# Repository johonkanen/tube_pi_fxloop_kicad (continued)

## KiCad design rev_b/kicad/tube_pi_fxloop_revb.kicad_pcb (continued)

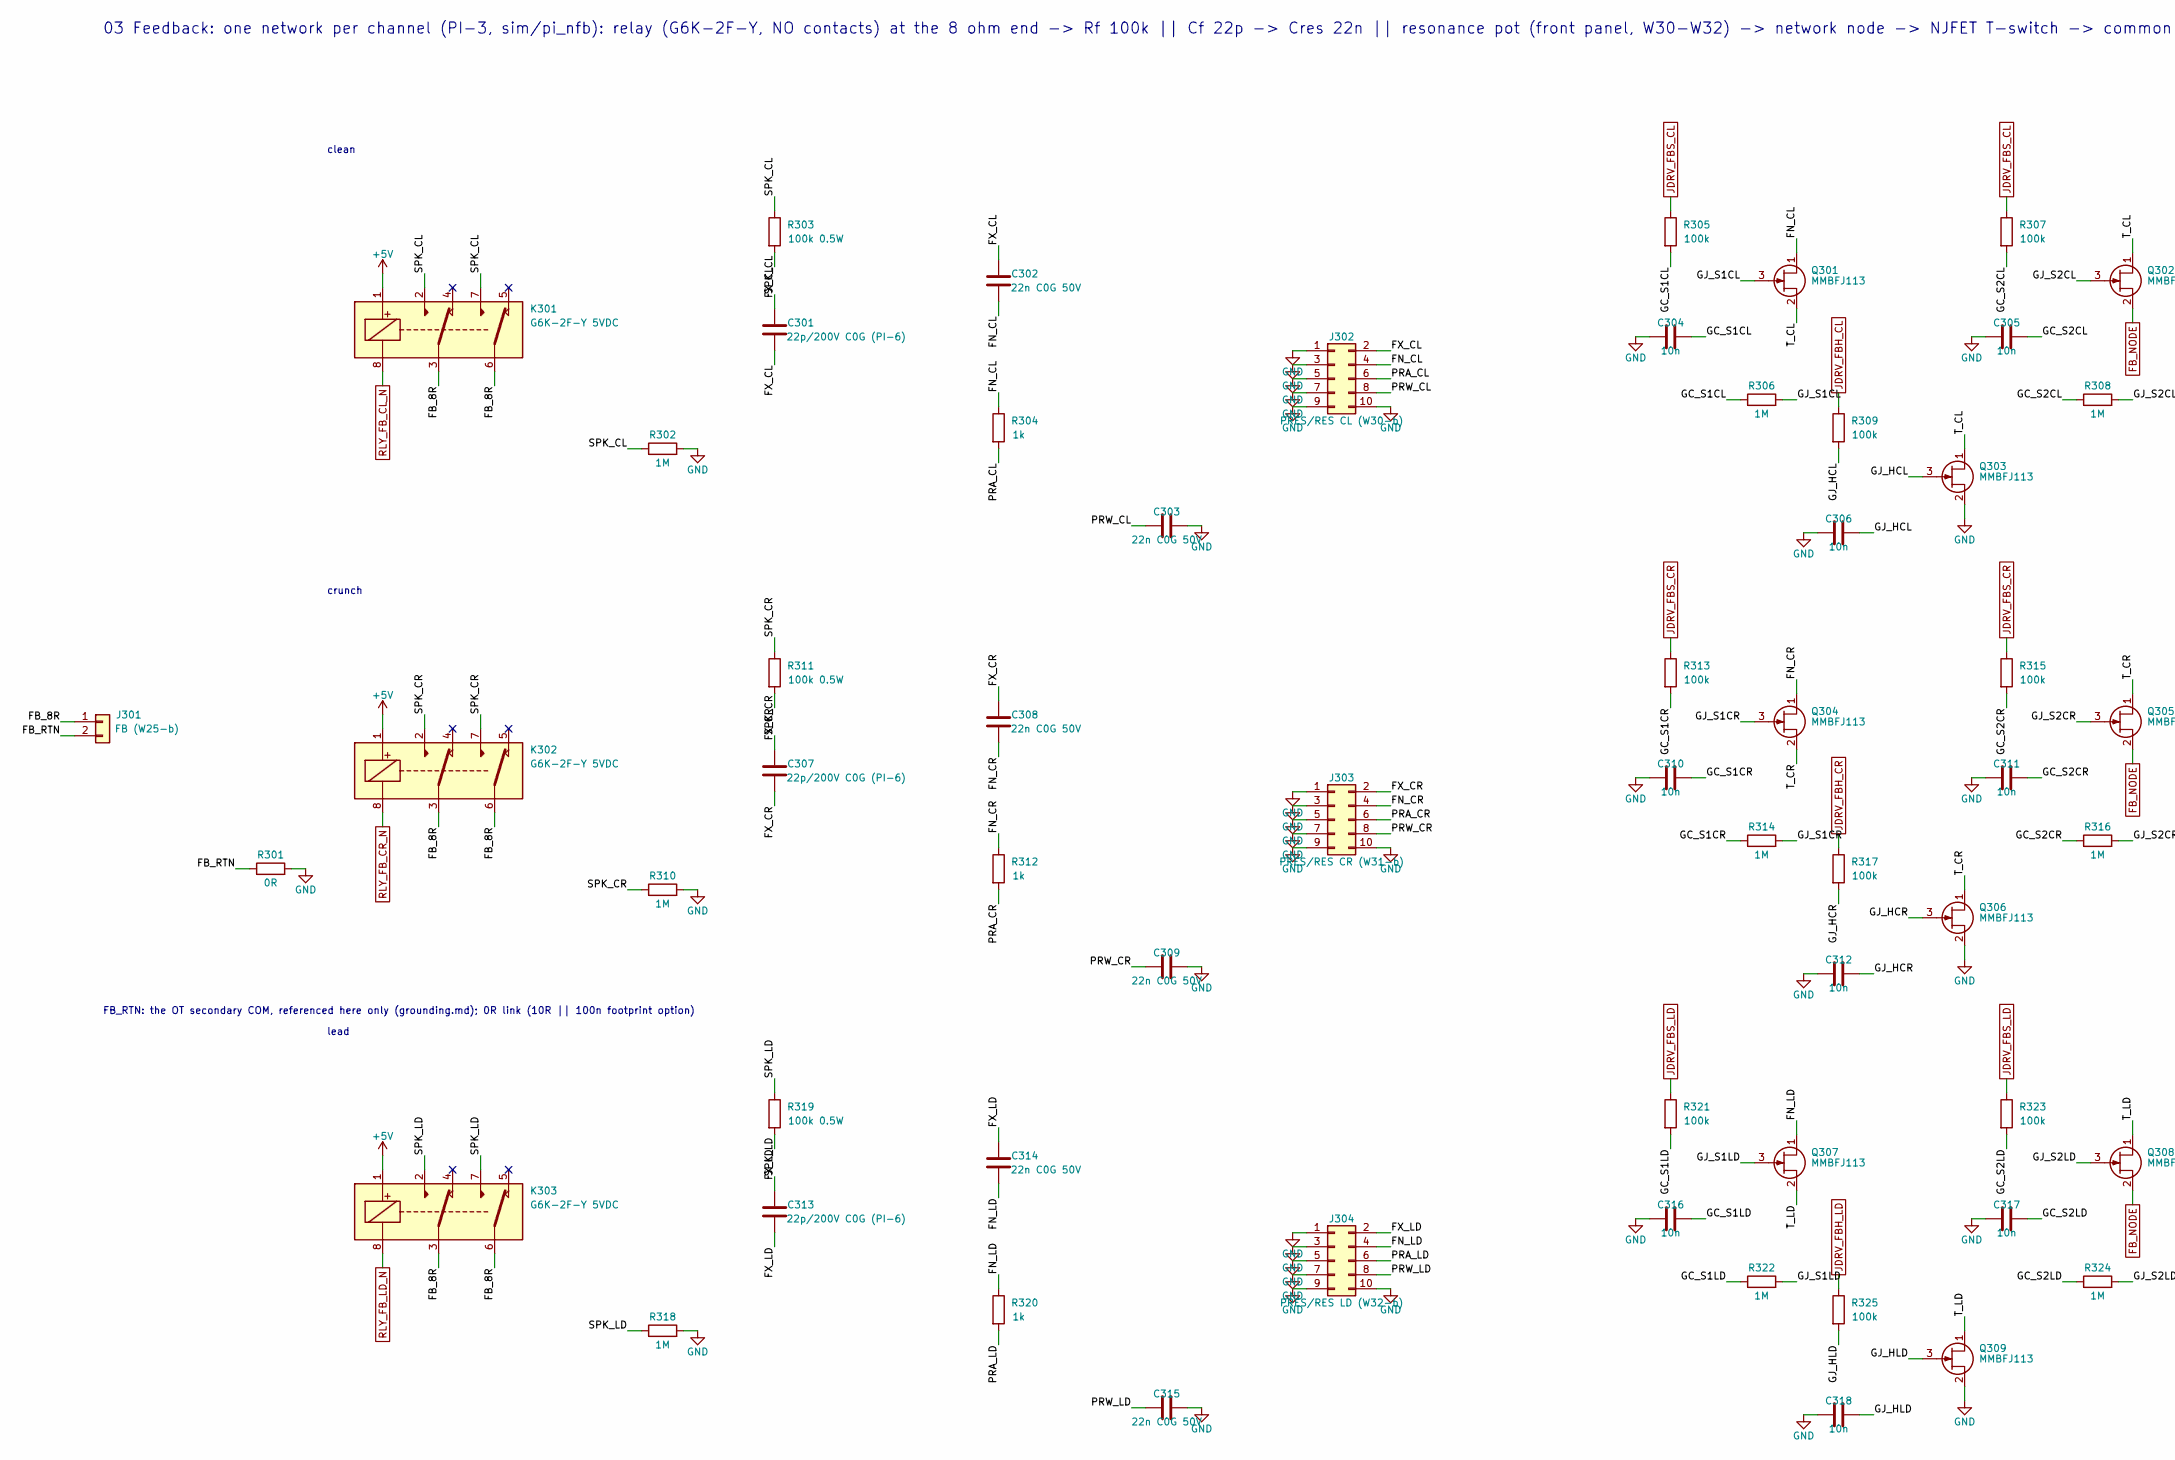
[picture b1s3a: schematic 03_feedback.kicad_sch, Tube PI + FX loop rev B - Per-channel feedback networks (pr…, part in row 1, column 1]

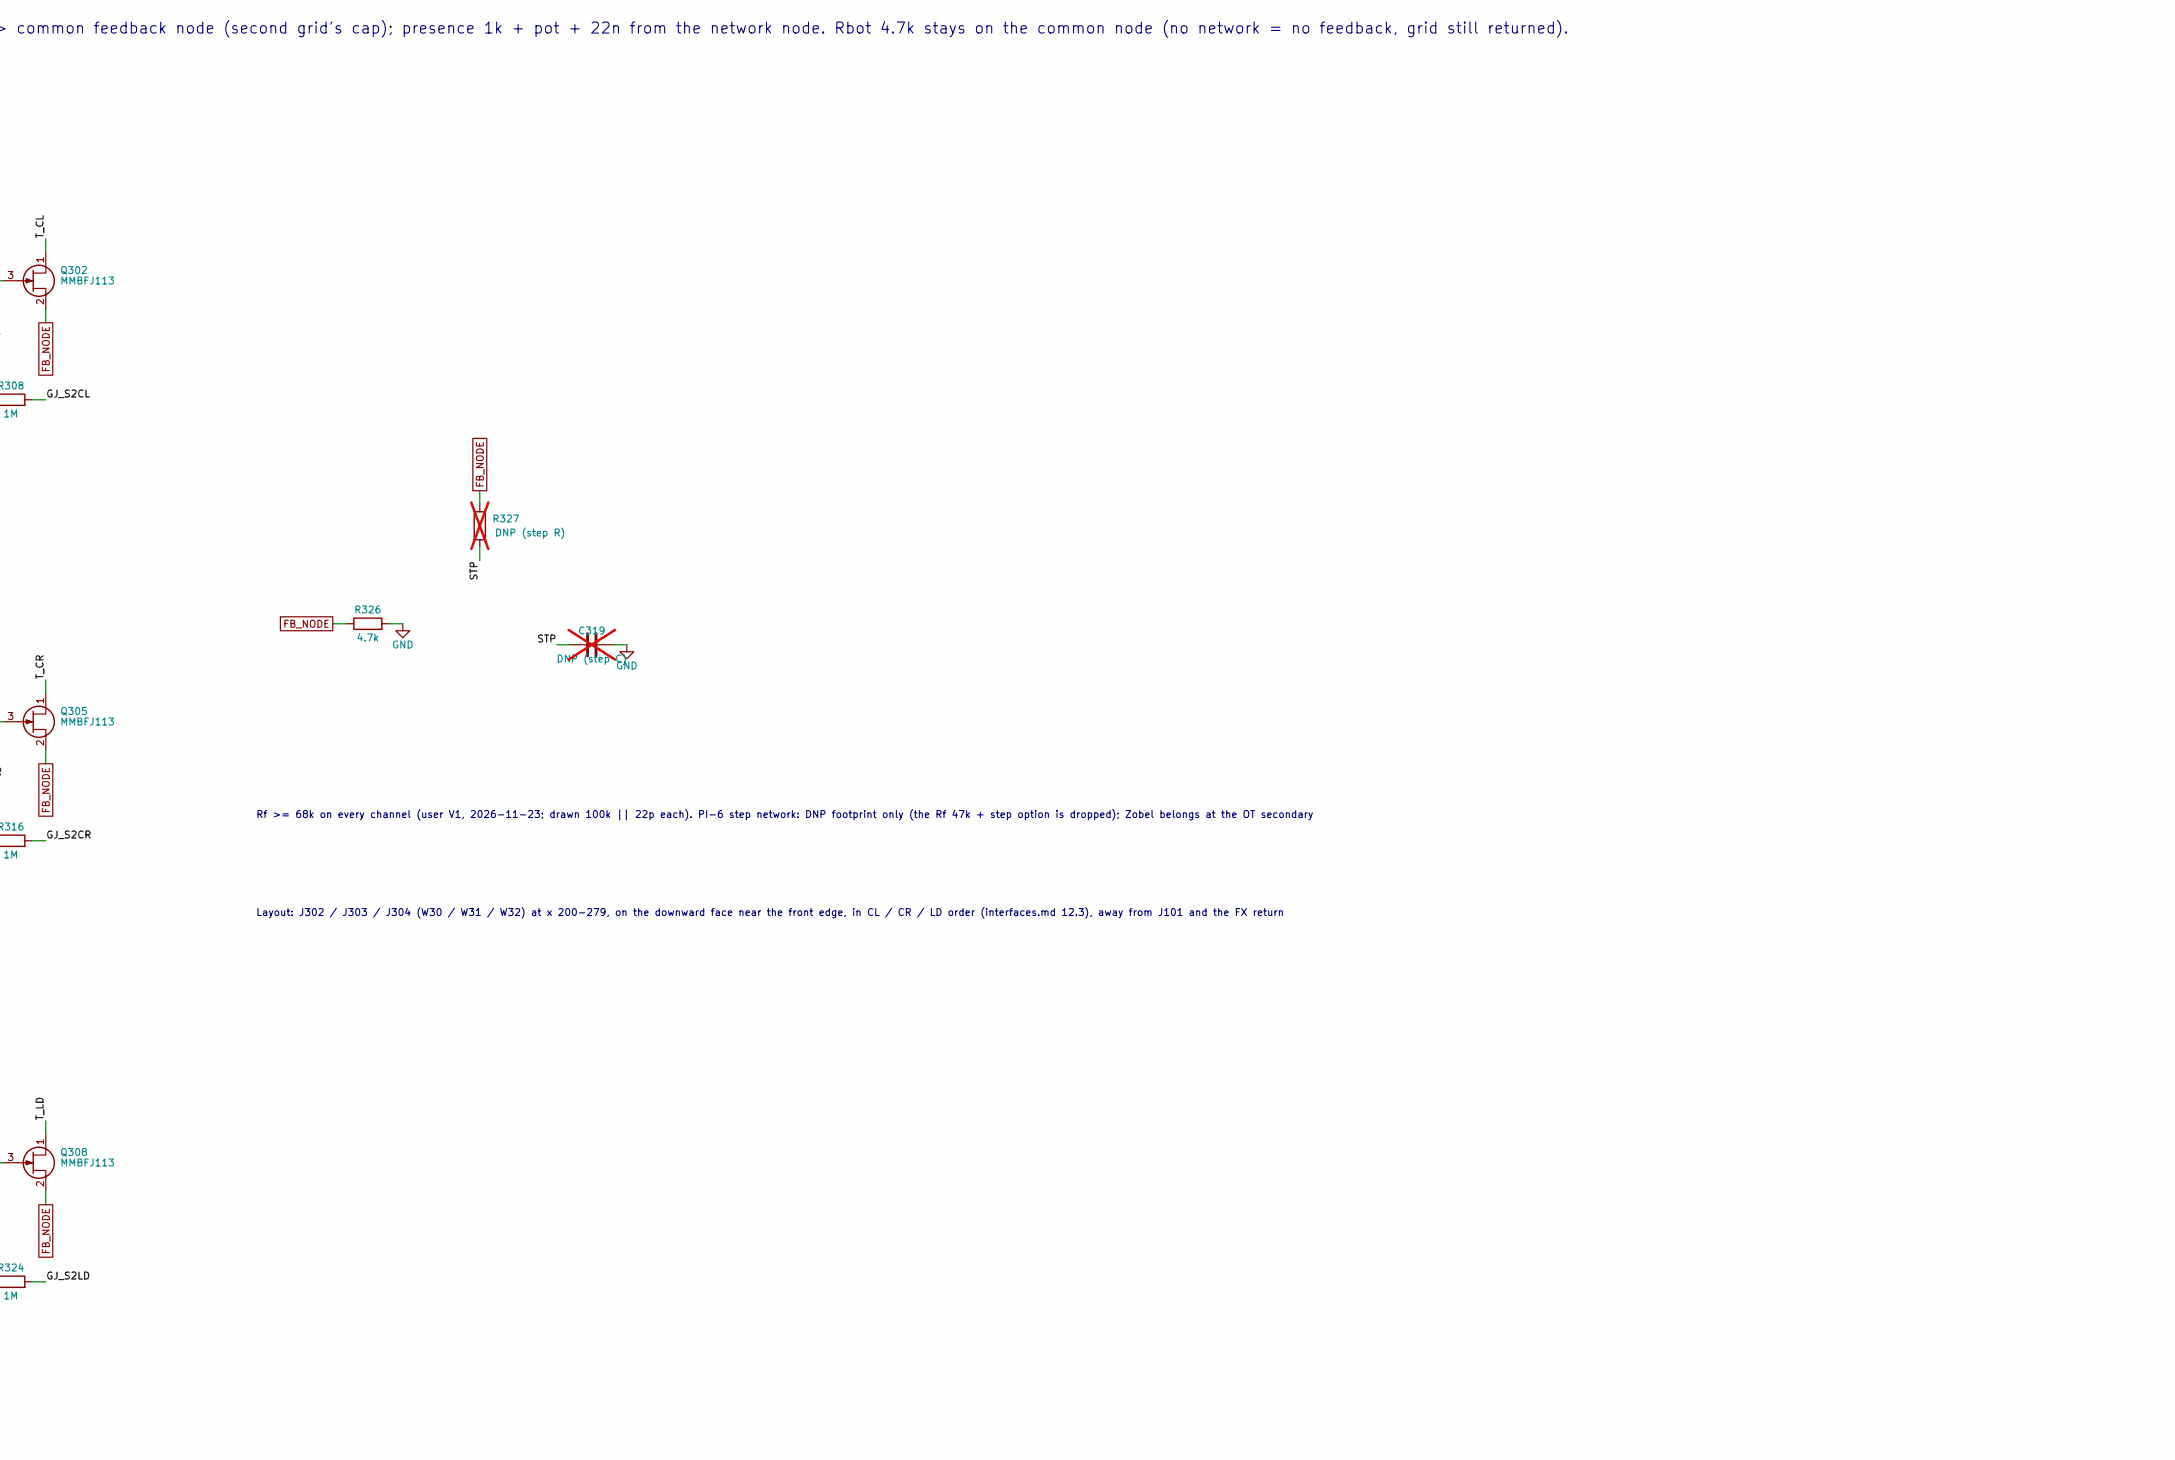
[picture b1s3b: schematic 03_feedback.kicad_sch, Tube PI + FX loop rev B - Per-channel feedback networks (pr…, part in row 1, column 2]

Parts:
C301, C307, C313: 22p/200V C0G (PI-6); C_1206_3216Metric
C302, C303, C308, C309, C314, C315: 22n C0G 50V; C_1206_3216Metric
C304, C305, C306, C310, C311, C312, C316, C317, C318: 10n; C_0603_1608Metric
C319: DNP (step C); C_0805_2012Metric; not fitted
J301: FB (W25-b); Molex_KK-396_A-41791-0002_1x02_P3.96mm_Vertical
J302: PRES/RES CL (W30-b); IDC-Header_2x05_P2.54mm_Vertical
J303: PRES/RES CR (W31-b); IDC-Header_2x05_P2.54mm_Vertical
J304: PRES/RES LD (W32-b); IDC-Header_2x05_P2.54mm_Vertical
K301, K302, K303: G6K-2F-Y 5VDC; Relay_DPDT_Omron_G6K-2F-Y
Q301, Q302, Q303, Q304, Q305, Q306, Q307, Q308, Q309: MMBFJ113; SOT-23
R301: 0R; R_0805_2012Metric
R302, R310, R318: 1M; R_0805_2012Metric
R303, R311, R319: 100k 0.5W; R_1206_3216Metric
R304, R312, R320: 1k; R_0805_2012Metric
R305, R307, R309, R313, R315, R317, R321, R323, R325: 100k; R_0603_1608Metric
R306, R308, R314, R316, R322, R324: 1M; R_0603_1608Metric
R326: 4.7k; R_0805_2012Metric
R327: DNP (step R); R_0805_2012Metric; not fitted

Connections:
+5V: K301.1, K302.1, K303.1; also elsewhere on the board
/03 Per-channel feedback networks (presence and resonance)/FB_8R: J301.1, K301.3, K301.6, K302.3, K302.6, K303.3, K303.6
/03 Per-channel feedback networks (presence and resonance)/FB_RTN: J301.2, R301.1
/03 Per-channel feedback networks (presence and resonance)/FN_CL: C302.2, J302.4, Q301.1 (D), R304.1
/03 Per-channel feedback networks (presence and resonance)/FN_CR: C308.2, J303.4, Q304.1 (D), R312.1
/03 Per-channel feedback networks (presence and resonance)/FN_LD: C314.2, J304.4, Q307.1 (D), R320.1
/03 Per-channel feedback networks (presence and resonance)/FX_CL: C301.2, C302.1, J302.2, R303.2
/03 Per-channel feedback networks (presence and resonance)/FX_CR: C307.2, C308.1, J303.2, R311.2
/03 Per-channel feedback networks (presence and resonance)/FX_LD: C313.2, C314.1, J304.2, R319.2
/03 Per-channel feedback networks (presence and resonance)/GC_S1CL: C304.1, R305.2, R306.1
/03 Per-channel feedback networks (presence and resonance)/GC_S1CR: C310.1, R313.2, R314.1
/03 Per-channel feedback networks (presence and resonance)/GC_S1LD: C316.1, R321.2, R322.1
/03 Per-channel feedback networks (presence and resonance)/GC_S2CL: C305.1, R307.2, R308.1
/03 Per-channel feedback networks (presence and resonance)/GC_S2CR: C311.1, R315.2, R316.1
/03 Per-channel feedback networks (presence and resonance)/GC_S2LD: C317.1, R323.2, R324.1
/03 Per-channel feedback networks (presence and resonance)/GJ_HCL: C306.1, Q303.3 (G), R309.2
/03 Per-channel feedback networks (presence and resonance)/GJ_HCR: C312.1, Q306.3 (G), R317.2
/03 Per-channel feedback networks (presence and resonance)/GJ_HLD: C318.1, Q309.3 (G), R325.2
/03 Per-channel feedback networks (presence and resonance)/GJ_S1CL: Q301.3 (G), R306.2
/03 Per-channel feedback networks (presence and resonance)/GJ_S1CR: Q304.3 (G), R314.2
/03 Per-channel feedback networks (presence and resonance)/GJ_S1LD: Q307.3 (G), R322.2
/03 Per-channel feedback networks (presence and resonance)/GJ_S2CL: Q302.3 (G), R308.2
/03 Per-channel feedback networks (presence and resonance)/GJ_S2CR: Q305.3 (G), R316.2
/03 Per-channel feedback networks (presence and resonance)/GJ_S2LD: Q308.3 (G), R324.2
/03 Per-channel feedback networks (presence and resonance)/PRA_CL: J302.6, R304.2
/03 Per-channel feedback networks (presence and resonance)/PRA_CR: J303.6, R312.2
/03 Per-channel feedback networks (presence and resonance)/PRA_LD: J304.6, R320.2
/03 Per-channel feedback networks (presence and resonance)/PRW_CL: C303.1, J302.8
/03 Per-channel feedback networks (presence and resonance)/PRW_CR: C309.1, J303.8
/03 Per-channel feedback networks (presence and resonance)/PRW_LD: C315.1, J304.8
/03 Per-channel feedback networks (presence and resonance)/SPK_CL: C301.1, K301.2, K301.7, R302.1, R303.1
/03 Per-channel feedback networks (presence and resonance)/SPK_CR: C307.1, K302.2, K302.7, R310.1, R311.1
/03 Per-channel feedback networks (presence and resonance)/SPK_LD: C313.1, K303.2, K303.7, R318.1, R319.1
/03 Per-channel feedback networks (presence and resonance)/STP: C319.1, R327.2
/03 Per-channel feedback networks (presence and resonance)/T_CL: Q301.2 (S), Q302.1 (D), Q303.1 (D)
/03 Per-channel feedback networks (presence and resonance)/T_CR: Q304.2 (S), Q305.1 (D), Q306.1 (D)
/03 Per-channel feedback networks (presence and resonance)/T_LD: Q307.2 (S), Q308.1 (D), Q309.1 (D)
FB_NODE: Q302.2 (S), Q305.2 (S), Q308.2 (S), R326.1, R327.1; also elsewhere on the board
GND: C303.2, C304.2, C305.2, C306.2, C309.2, C310.2, C311.2, C312.2, C315.2, C316.2, C317.2, C318.2, C319.2, J302.1, J302.3, J302.5, J302.7, J302.9, J302.10, J303.1, J303.3, J303.5, J303.7, J303.9, J303.10, J304.1, J304.3, J304.5, J304.7, J304.9, J304.10, Q303.2 (S), Q306.2 (S), Q309.2 (S), R301.2, R302.2, R310.2, R318.2, R326.2; also elsewhere on the board
JDRV_FBH_CL: R309.1; also elsewhere on the board
JDRV_FBH_CR: R317.1; also elsewhere on the board
JDRV_FBH_LD: R325.1; also elsewhere on the board
JDRV_FBS_CL: R305.1, R307.1; also elsewhere on the board
JDRV_FBS_CR: R313.1, R315.1; also elsewhere on the board
JDRV_FBS_LD: R321.1, R323.1; also elsewhere on the board
RLY_FB_CL_N: K301.8; also elsewhere on the board
RLY_FB_CR_N: K302.8; also elsewhere on the board
RLY_FB_LD_N: K303.8; also elsewhere on the board

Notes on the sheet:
03 Feedback: one network per channel (PI-3, sim/pi_nfb): relay (G6K-2F-Y, NO contacts) at the 8 ohm end -> Rf 100k || Cf 22p -> Cres 22n || resonance pot (front panel, W30-W32) -> network node -> NJFET T-switch -> common feedback node (second grid's cap); presence 1k + pot + 22n from the network no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
FB_RTN: the OT secondary COM, referenced here only (grounding.md); 0R link (10R || 100n footprint option)
clean
crunch
lead
Rf >= 68k on every channel (user V1, 2026-11-23; drawn 100k || 22p each). PI-6 step network: DNP footprint only (the Rf 47k + step option is dropped); Zobel belongs at the OT secondary
Layout: J302 / J303 / J304 (W30 / W31 / W32) at x 200-279, on the downward face near the front edge, in CL / CR / LD order (interfaces.md 12.3), away from J101 and the FX return

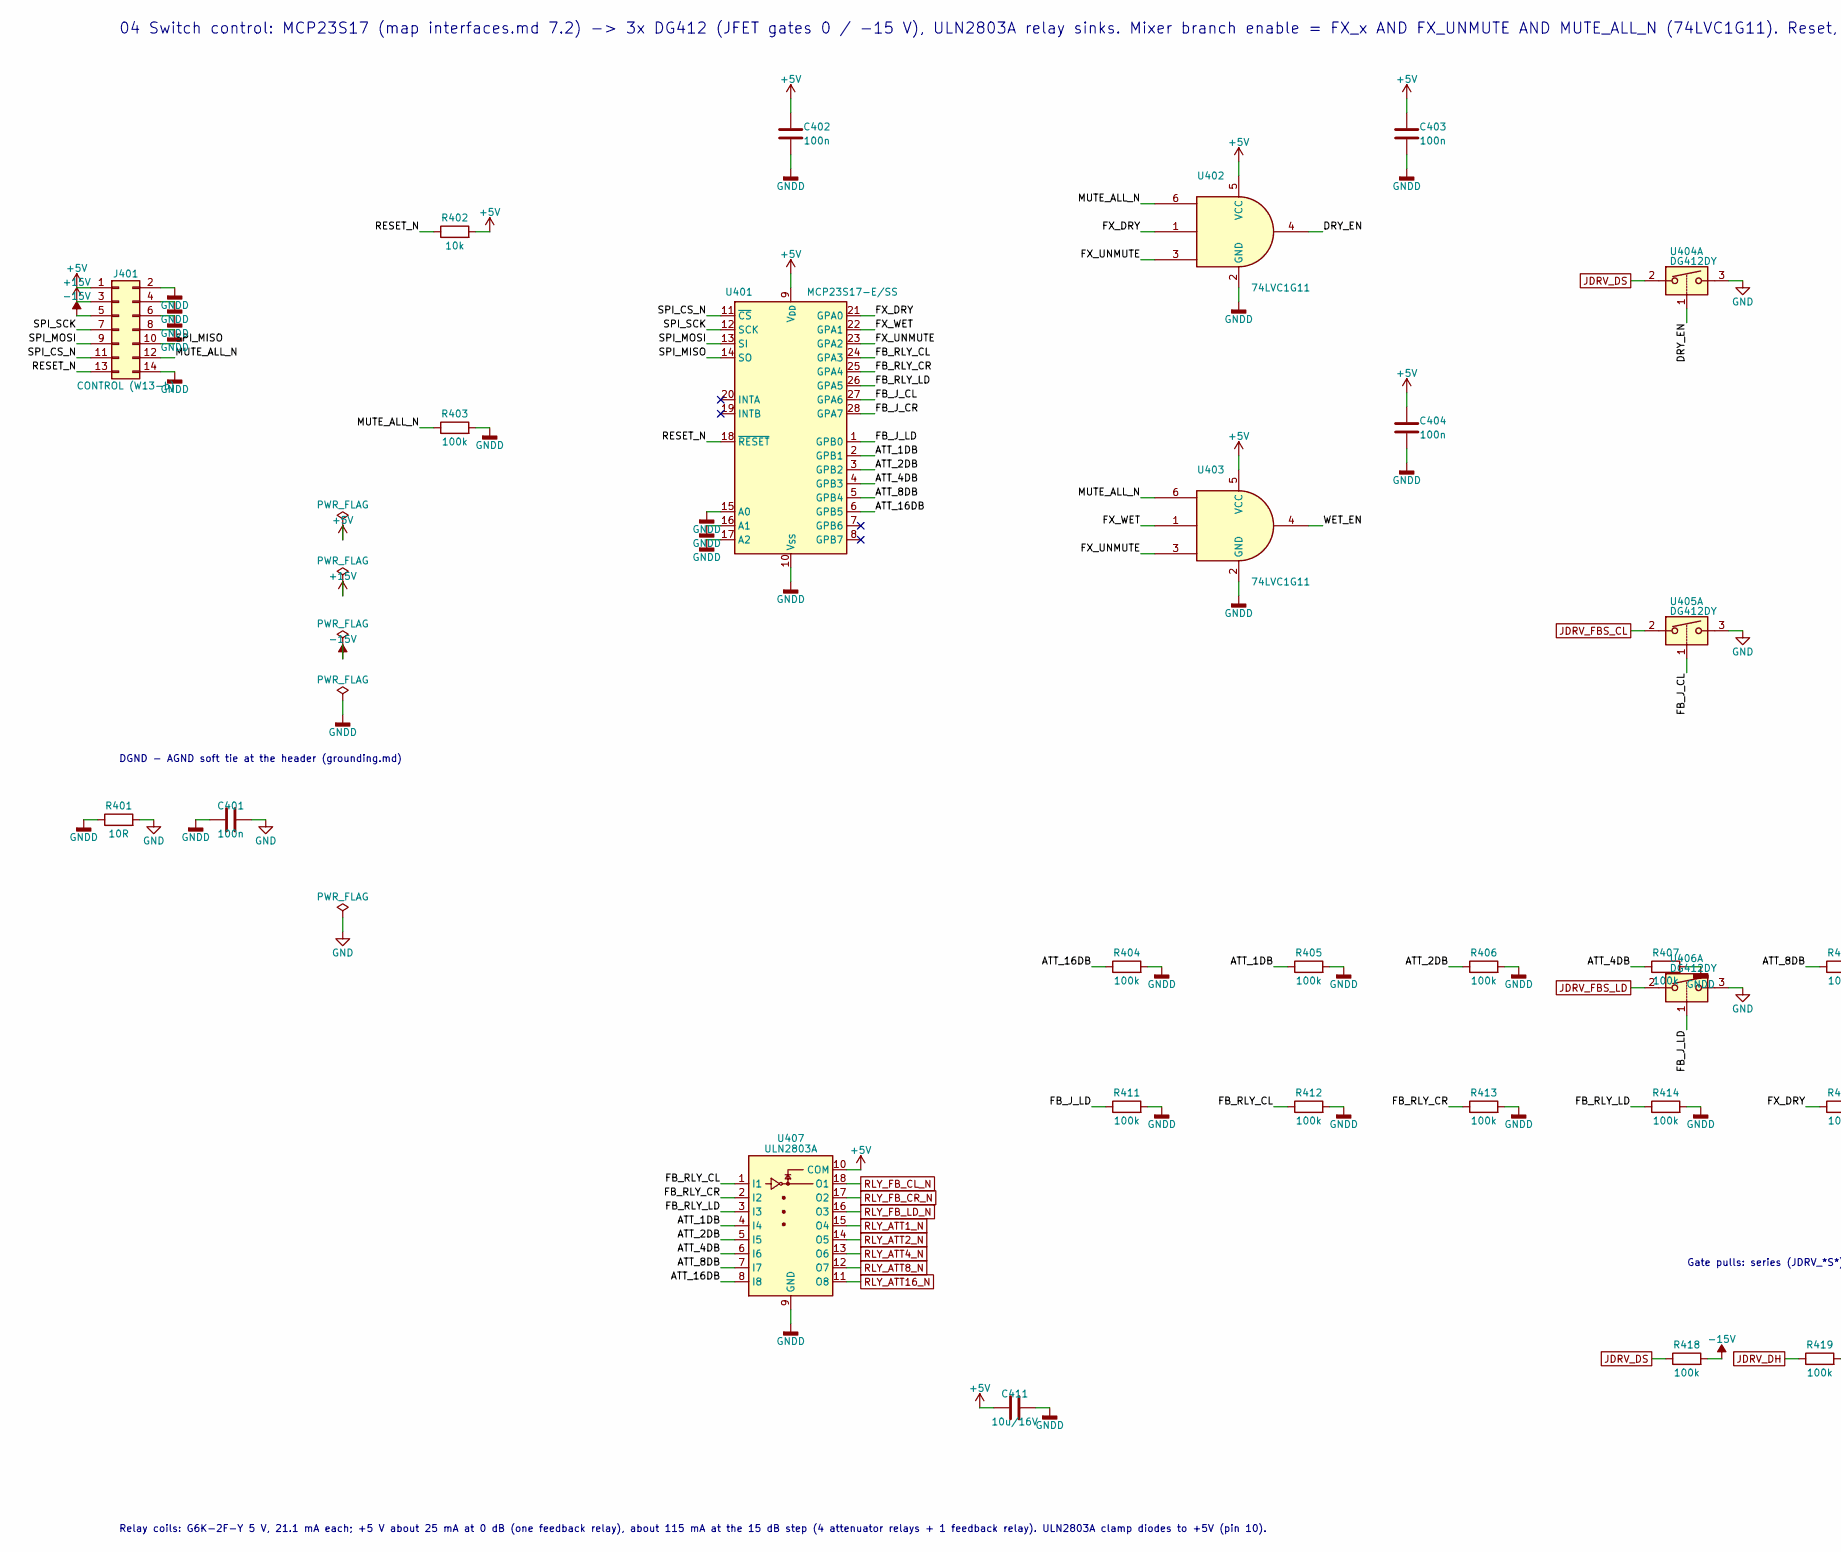
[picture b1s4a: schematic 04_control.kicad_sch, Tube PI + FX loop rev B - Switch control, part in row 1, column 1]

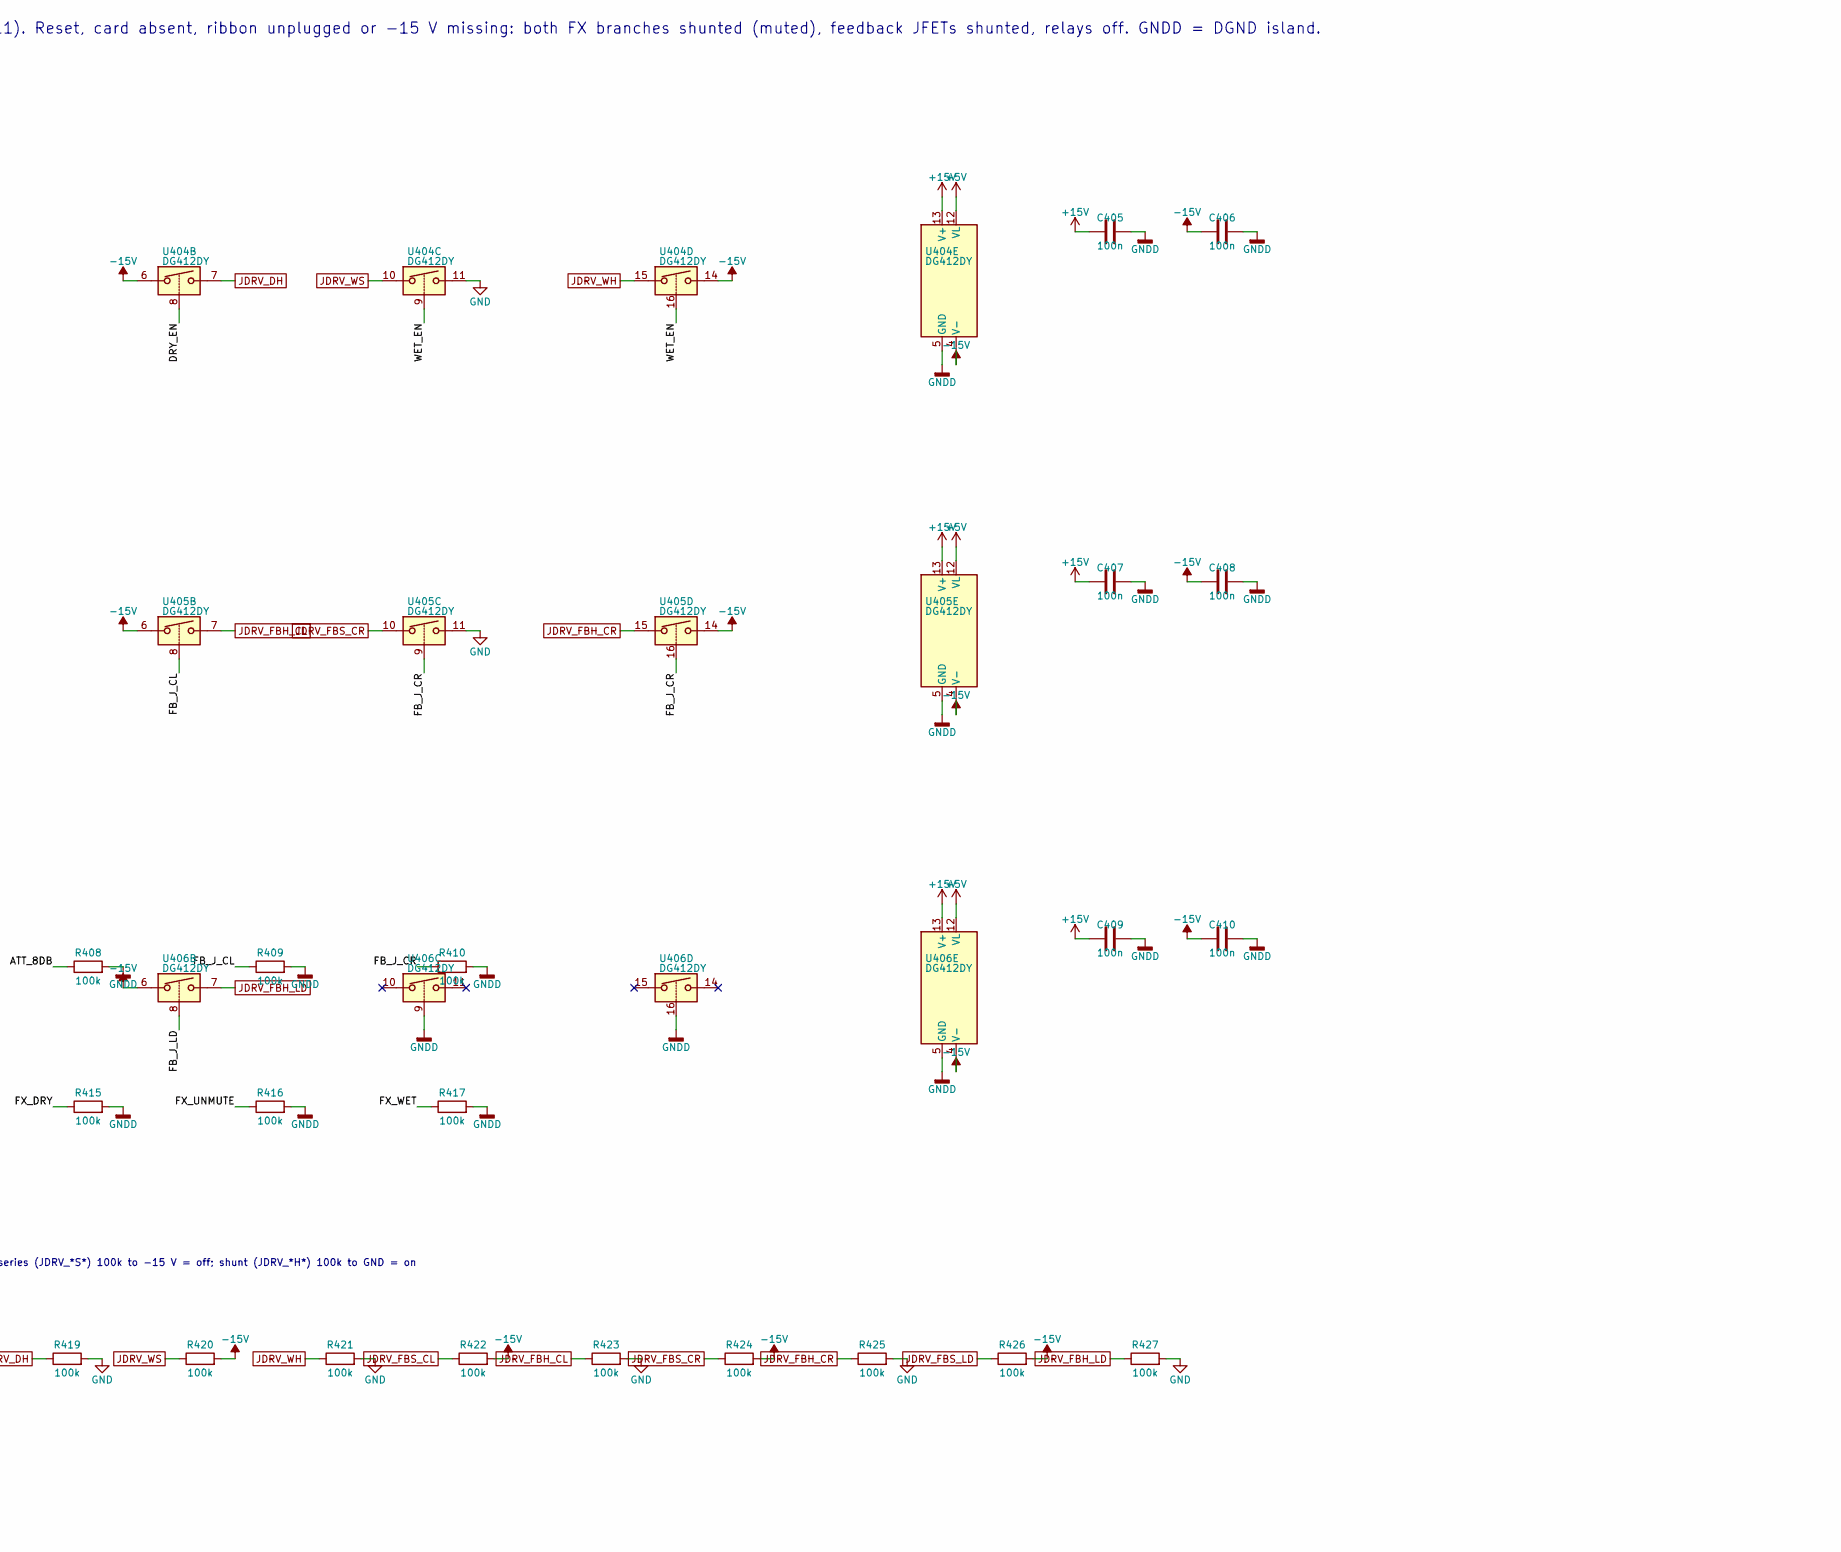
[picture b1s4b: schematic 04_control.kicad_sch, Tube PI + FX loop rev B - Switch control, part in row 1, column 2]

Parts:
C401, C402, C403, C404, C405, C406, C407, C408, C409, C410: 100n; C_0603_1608Metric
C411: 10u/16V; C_0805_2012Metric
J401: CONTROL (W13-b); IDC-Header_2x07_P2.54mm_Vertical
R401: 10R; R_0603_1608Metric
R402: 10k; R_0603_1608Metric
R403, R404, R405, R406, R407, R408, R409, R410, R411, R412, R413, R414, R415, R416, R417, R418, R419, R420, R421, R422, R423, R424, R425, R426, R427: 100k; R_0603_1608Metric
U401: MCP23S17-E/SS; SSOP-28_5.3x10.2mm_P0.65mm
U402, U403: 74LVC1G11; SOT-23-6
U404, U405, U406: DG412DY; SOIC-16_3.9x9.9mm_P1.27mm
U407: ULN2803A; SOIC-18W_7.5x11.6mm_P1.27mm

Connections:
+5V: C402.1, C403.1, C404.1, C411.1, J401.1, R402.2, U401.9 (V_{DD}), U402.5 (VCC), U403.5 (VCC), U404.12 (VL), U405.12 (VL), U406.12 (VL), U407.10 (COM); also elsewhere on the board
+15V: C405.1, C407.1, C409.1, J401.3, U404.13 (V+), U405.13 (V+), U406.13 (V+)
-15V: C406.1, C408.1, C410.1, J401.5, R418.2, R420.2, R422.2, R424.2, R426.2, U404.4 (V-), U404.6, U404.14, U405.4 (V-), U405.6, U405.14, U406.4 (V-), U406.6; also elsewhere on the board
/04 Switch control/ATT_1DB: R405.1, U401.2 (GPB1), U407.4 (I4)
/04 Switch control/ATT_2DB: R406.1, U401.3 (GPB2), U407.5 (I5)
/04 Switch control/ATT_4DB: R407.1, U401.4 (GPB3), U407.6 (I6)
/04 Switch control/ATT_8DB: R408.1, U401.5 (GPB4), U407.7 (I7)
/04 Switch control/ATT_16DB: R404.1, U401.6 (GPB5), U407.8 (I8)
/04 Switch control/DRY_EN: U402.4, U404.1, U404.8
/04 Switch control/FB_J_CL: R409.1, U401.27 (GPA6), U405.1, U405.8
/04 Switch control/FB_J_CR: R410.1, U401.28 (GPA7), U405.9, U405.16
/04 Switch control/FB_J_LD: R411.1, U401.1 (GPB0), U406.1, U406.8
/04 Switch control/FB_RLY_CL: R412.1, U401.24 (GPA3), U407.1 (I1)
/04 Switch control/FB_RLY_CR: R413.1, U401.25 (GPA4), U407.2 (I2)
/04 Switch control/FB_RLY_LD: R414.1, U401.26 (GPA5), U407.3 (I3)
/04 Switch control/FX_DRY: R415.1, U401.21 (GPA0), U402.1
/04 Switch control/FX_UNMUTE: R416.1, U401.23 (GPA2), U402.3, U403.3
/04 Switch control/FX_WET: R417.1, U401.22 (GPA1), U403.1
/04 Switch control/MUTE_ALL_N: J401.12, R403.1, U402.6, U403.6
/04 Switch control/RESET_N: J401.13, R402.1, U401.18 (~RESET)
/04 Switch control/SPI_CS_N: J401.11, U401.11 (~CS)
/04 Switch control/SPI_MISO: J401.10, U401.14 (SO)
/04 Switch control/SPI_MOSI: J401.9, U401.13 (SI)
/04 Switch control/SPI_SCK: J401.7, U401.12 (SCK)
/04 Switch control/WET_EN: U403.4, U404.9, U404.16
GND: C401.2, R401.2, R419.2, R421.2, R423.2, R425.2, R427.2, U404.3, U404.11, U405.3, U405.11, U406.3; also elsewhere on the board
GNDD: C401.1, C402.2, C403.2, C404.2, C405.2, C406.2, C407.2, C408.2, C409.2, C410.2, C411.2, J401.2, J401.4, J401.6, J401.8, J401.14, R401.1, R403.2, R404.2, R405.2, R406.2, R407.2, R408.2, R409.2, R410.2, R411.2, R412.2, R413.2, R414.2, R415.2, R416.2, R417.2, U401.10 (V_{SS}), U401.15 (A0), U401.16 (A1), U401.17 (A2), U402.2 (GND), U403.2 (GND), U404.5 (GND), U405.5 (GND), U406.5 (GND), U406.9, U406.16, U407.9 (GND)
JDRV_DH: R419.1, U404.7; also elsewhere on the board
JDRV_DS: R418.1, U404.2; also elsewhere on the board
JDRV_FBH_CL: R423.1, U405.7; also elsewhere on the board
JDRV_FBH_CR: R425.1, U405.15; also elsewhere on the board
JDRV_FBH_LD: R427.1, U406.7; also elsewhere on the board
JDRV_FBS_CL: R422.1, U405.2; also elsewhere on the board
JDRV_FBS_CR: R424.1, U405.10; also elsewhere on the board
JDRV_FBS_LD: R426.1, U406.2; also elsewhere on the board
JDRV_WH: R421.1, U404.15; also elsewhere on the board
JDRV_WS: R420.1, U404.10; also elsewhere on the board
RLY_ATT1_N: U407.15 (O4); also elsewhere on the board
RLY_ATT2_N: U407.14 (O5); also elsewhere on the board
RLY_ATT4_N: U407.13 (O6); also elsewhere on the board
RLY_ATT8_N: U407.12 (O7); also elsewhere on the board
RLY_ATT16_N: U407.11 (O8); also elsewhere on the board
RLY_FB_CL_N: U407.18 (O1); also elsewhere on the board
RLY_FB_CR_N: U407.17 (O2); also elsewhere on the board
RLY_FB_LD_N: U407.16 (O3); also elsewhere on the board

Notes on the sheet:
04 Switch control: MCP23S17 (map interfaces.md 7.2) -> 3x DG412 (JFET gates 0 / -15 V), ULN2803A relay sinks. Mixer branch enable = FX_x AND FX_UNMUTE AND MUTE_ALL_N (74LVC1G11). Reset, card absent, ribbon unplugged or -15 V missing: both FX branches shunted (muted), feedback JFETs shunted, relays 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
DGND - AGND soft tie at the header (grounding.md)
Gate pulls: series (JDRV_*S*) 100k to -15 V = off; shunt (JDRV_*H*) 100k to GND = on
Relay coils: G6K-2F-Y 5 V, 21.1 mA each; +5 V about 25 mA at 0 dB (one feedback relay), about 115 mA at the 15 dB step (4 attenuator relays + 1 feedback relay). ULN2803A clamp diodes to +5V (pin 10).
